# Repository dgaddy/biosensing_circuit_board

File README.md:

These designs are for a low-cost biosensing board for measuring signals such as EMG, EEG, or ECG.

The board is designed to plug into an Adafruit Feather M4 Express and send the collected signals back to a computer over USB.

**Disclaimer:** Connecting electrical circuitry to your body can be dangerous.  I do not make any guarantees to the safety of this design.  Before building, you should conduct your own analysis of safety.

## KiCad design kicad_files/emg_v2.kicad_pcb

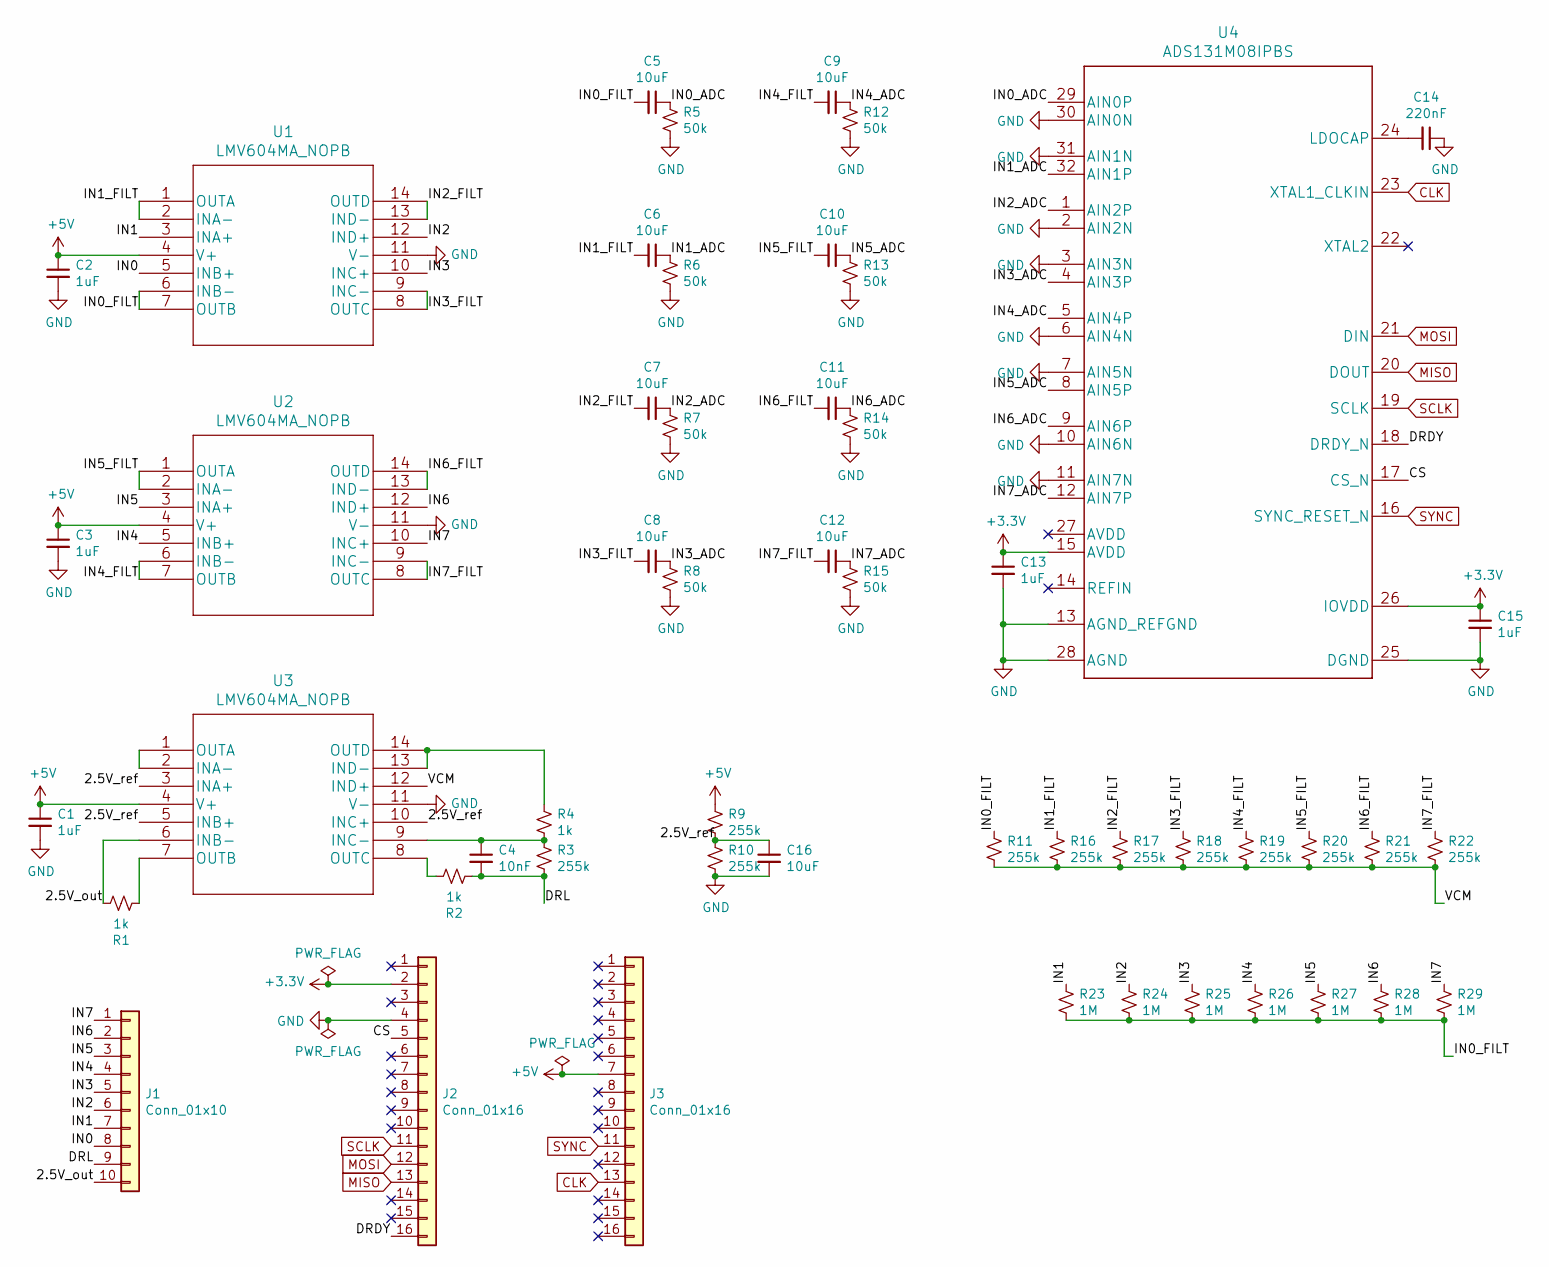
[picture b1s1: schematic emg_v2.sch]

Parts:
C1, C2, C3, C13, C15: 1uF; C_0603_1608Metric_Pad1.08x0.95mm_HandSolder
C4: 10nF; C_0603_1608Metric_Pad1.08x0.95mm_HandSolder
C5, C6, C7, C8, C9, C10, C11, C12, C16: 10uF; C_0603_1608Metric_Pad1.08x0.95mm_HandSolder
C14: 220nF; C_0603_1608Metric_Pad1.08x0.95mm_HandSolder
J1: Conn_01x10; PinHeader_1x10_P2.54mm_Vertical
J2, J3: Conn_01x16; PinSocket_1x16_P2.54mm_Vertical
R1, R2, R4: 1k; R_0603_1608Metric_Pad0.98x0.95mm_HandSolder
R3, R9, R10, R11, R16, R17, R18, R19, R20, R21, R22: 255k; R_0603_1608Metric_Pad0.98x0.95mm_HandSolder
R5, R6, R7, R8, R12, R13, R14, R15: 50k; R_0603_1608Metric_Pad0.98x0.95mm_HandSolder
R23, R24, R25, R26, R27, R28, R29: 1M; R_0603_1608Metric_Pad0.98x0.95mm_HandSolder
U1, U2, U3: LMV604MA_NOPB; SOIC-14_3.9x8.7mm_P1.27mm
U4: ADS131M08IPBS; LQFP-32_5x5mm_P0.5mm

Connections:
+3V3: C13.1, C15.1, J2.2, U4.15 (AVDD), U4.26 (IOVDD)
+5V: C1.1, C2.1, C3.1, J3.7, R9.1, U1.4 (V+), U2.4 (V+), U3.4 (V+)
/2.5V_out: J1.10, R1.1, U3.6 (INB-)
/2.5V_ref: C16.1, R9.2, R10.1, U3.3 (INA+), U3.5 (INB+), U3.10 (INC+)
/CS: J2.5, U4.17 (CS_N)
/DRDY: J2.16, U4.18 (DRDY_N)
/DRL: C4.2, J1.9, R2.2, R3.2
/IN0: J1.8, U1.5 (INB+)
/IN0_ADC: C5.1, R5.1, U4.29 (AIN0P)
/IN0_FILT: C5.2, R11.1, R23.2, R24.2, R25.2, R26.2, R27.2, R28.2, R29.2, U1.6 (INB-), U1.7 (OUTB)
/IN1: J1.7, R23.1, U1.3 (INA+)
/IN1_ADC: C6.1, R6.1, U4.32 (AIN1P)
/IN1_FILT: C6.2, R16.1, U1.1 (OUTA), U1.2 (INA-)
/IN2: J1.6, R24.1, U1.12 (IND+)
/IN2_ADC: C7.1, R7.1, U4.1 (AIN2P)
/IN2_FILT: C7.2, R17.1, U1.13 (IND-), U1.14 (OUTD)
/IN3: J1.5, R25.1, U1.10 (INC+)
/IN3_ADC: C8.1, R8.1, U4.4 (AIN3P)
/IN3_FILT: C8.2, R18.1, U1.8 (OUTC), U1.9 (INC-)
/IN4: J1.4, R26.1, U2.5 (INB+)
/IN4_ADC: C9.1, R12.1, U4.5 (AIN4P)
/IN4_FILT: C9.2, R19.1, U2.6 (INB-), U2.7 (OUTB)
/IN5: J1.3, R27.1, U2.3 (INA+)
/IN5_ADC: C10.1, R13.1, U4.8 (AIN5P)
/IN5_FILT: C10.2, R20.1, U2.1 (OUTA), U2.2 (INA-)
/IN6: J1.2, R28.1, U2.12 (IND+)
/IN6_ADC: C11.1, R14.1, U4.9 (AIN6P)
/IN6_FILT: C11.2, R21.1, U2.13 (IND-), U2.14 (OUTD)
/IN7: J1.1, R29.1, U2.10 (INC+)
/IN7_ADC: C12.1, R15.1, U4.12 (AIN7P)
/IN7_FILT: C12.2, R22.1, U2.8 (OUTC), U2.9 (INC-)
/VCM: R11.2, R16.2, R17.2, R18.2, R19.2, R20.2, R21.2, R22.2, U3.12 (IND+)
CLK: J3.13, U4.23 (XTAL1_CLKIN)
GND: C1.2, C2.2, C3.2, C13.2, C14.1, C15.2, C16.2, J2.4, R5.2, R6.2, R7.2, R8.2, R10.2, R12.2, R13.2, R14.2, R15.2, U1.11 (V-), U2.11 (V-), U3.11 (V-), U4.2 (AIN2N), U4.3 (AIN3N), U4.6 (AIN4N), U4.7 (AIN5N), U4.10 (AIN6N), U4.11 (AIN7N), U4.13 (AGND_REFGND), U4.25 (DGND), U4.28 (AGND), U4.30 (AIN0N), U4.31 (AIN1N)
MISO: J2.13, U4.20 (DOUT)
MOSI: J2.12, U4.21 (DIN)
unnamed: C4.1, R3.1, R4.2, U3.9 (INC-)
unnamed: C14.2, U4.24 (LDOCAP)
unnamed: R1.2, U3.7 (OUTB)
unnamed: R2.1, U3.8 (OUTC)
unnamed: R4.1, U3.13 (IND-), U3.14 (OUTD)
unnamed: U3.1 (OUTA), U3.2 (INA-)
SCLK: J2.11, U4.19 (SCLK)
SYNC: J3.11, U4.16 (SYNC_RESET_N)

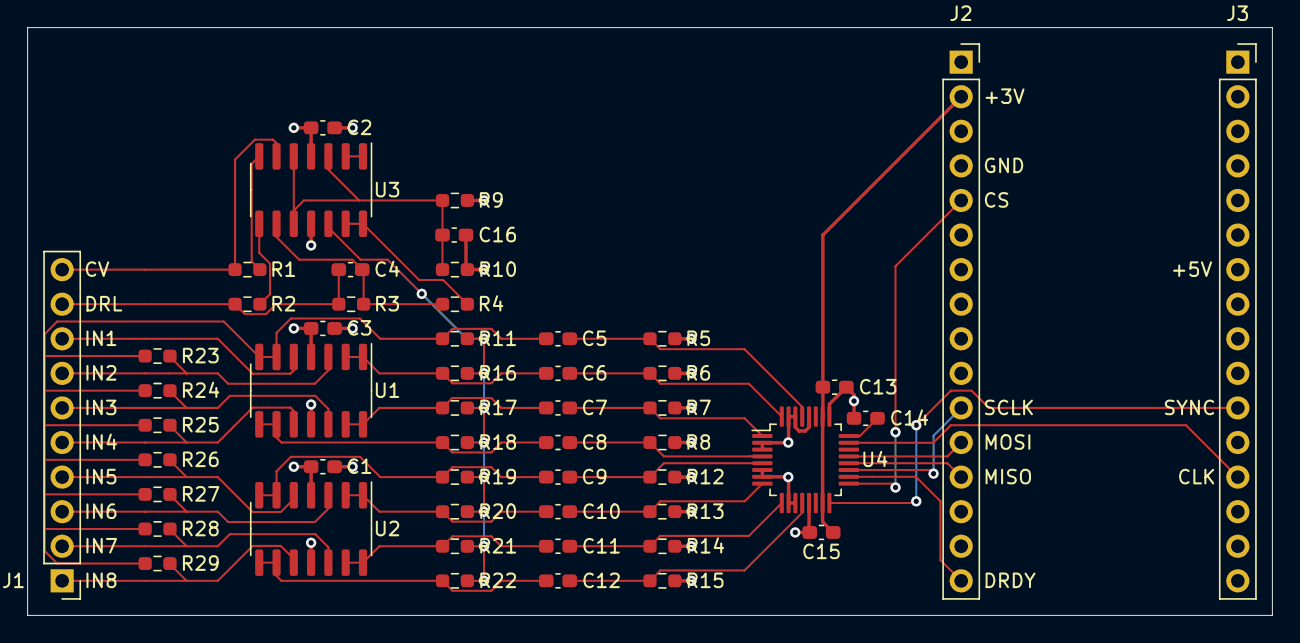
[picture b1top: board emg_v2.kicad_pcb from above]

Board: 4 copper layers, 91.4 x 43.2 mm, 52 parts (0 on the bottom side), 44 nets.

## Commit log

2022-06-27 Initial design release.
